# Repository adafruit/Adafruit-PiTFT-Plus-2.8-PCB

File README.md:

## Adafruit PiTFT 2.8 Plus PCB

&nbsp; 
<br/>
Click the image or links below to go to a specific product in the Adafruit shop.

PCB files for the Adafruit PiTFT Plus 2.8" Display. Format is EagleCAD schematic and board layout
* Resistive Screen https://www.adafruit.com/product/2298
* Capacitive Touch Screen https://www.adafruit.com/product/2423

### DESCRIPTION
Are these not the cutest little displays for the Raspberry Pi? They feature a 2.8" display with 320x240 16-bit color pixels and a  resistive touchscreen or capacitive touch overlay..

This updated design fits perfectly onto the Pi Zero, Pi 3, Pi 2 or Model A+, B+! (Any Pi with a 2x20 connector) Not for use with an old Pi 1 with 2x13 connector If you'd like to use a 2.8" display with the original Pi A or Pi B, check out the Model B version. This version also has all 40 pins GPIO pins brought out so you can connect a 40-pin GPIO cable underneath. Now that it's the same outline as a Pi 3/2/B+ it fits well on top of a Pi in our Raspberry Pi Enclosure base and can use our faceplate for a compact touchscreen Pi

The display and touchscreen uses the hardware I2C Pins (SDA & SCL), SPI pins (SCK, MOSI, MISO, CE0) as well as GPIO #25 and #24. All other GPIO are unused and you can still share the I2C pins with sensors, LED drivers, etc. Since we had a tiny bit of space, there's 4 slim tactile switches wired to four GPIOs, that you can use if you want to make a basic user interface. For example, you can use one as a power on/off button.

### License

Adafruit invests time and resources providing this open source design, please support Adafruit and open-source hardware by purchasing products from [Adafruit.com](https://www.adafruit.com)!

Creative Commons Attribution, Share-Alike license, check license.txt for more information All text above must be included in any redistribution - 
See license.txt for more information.

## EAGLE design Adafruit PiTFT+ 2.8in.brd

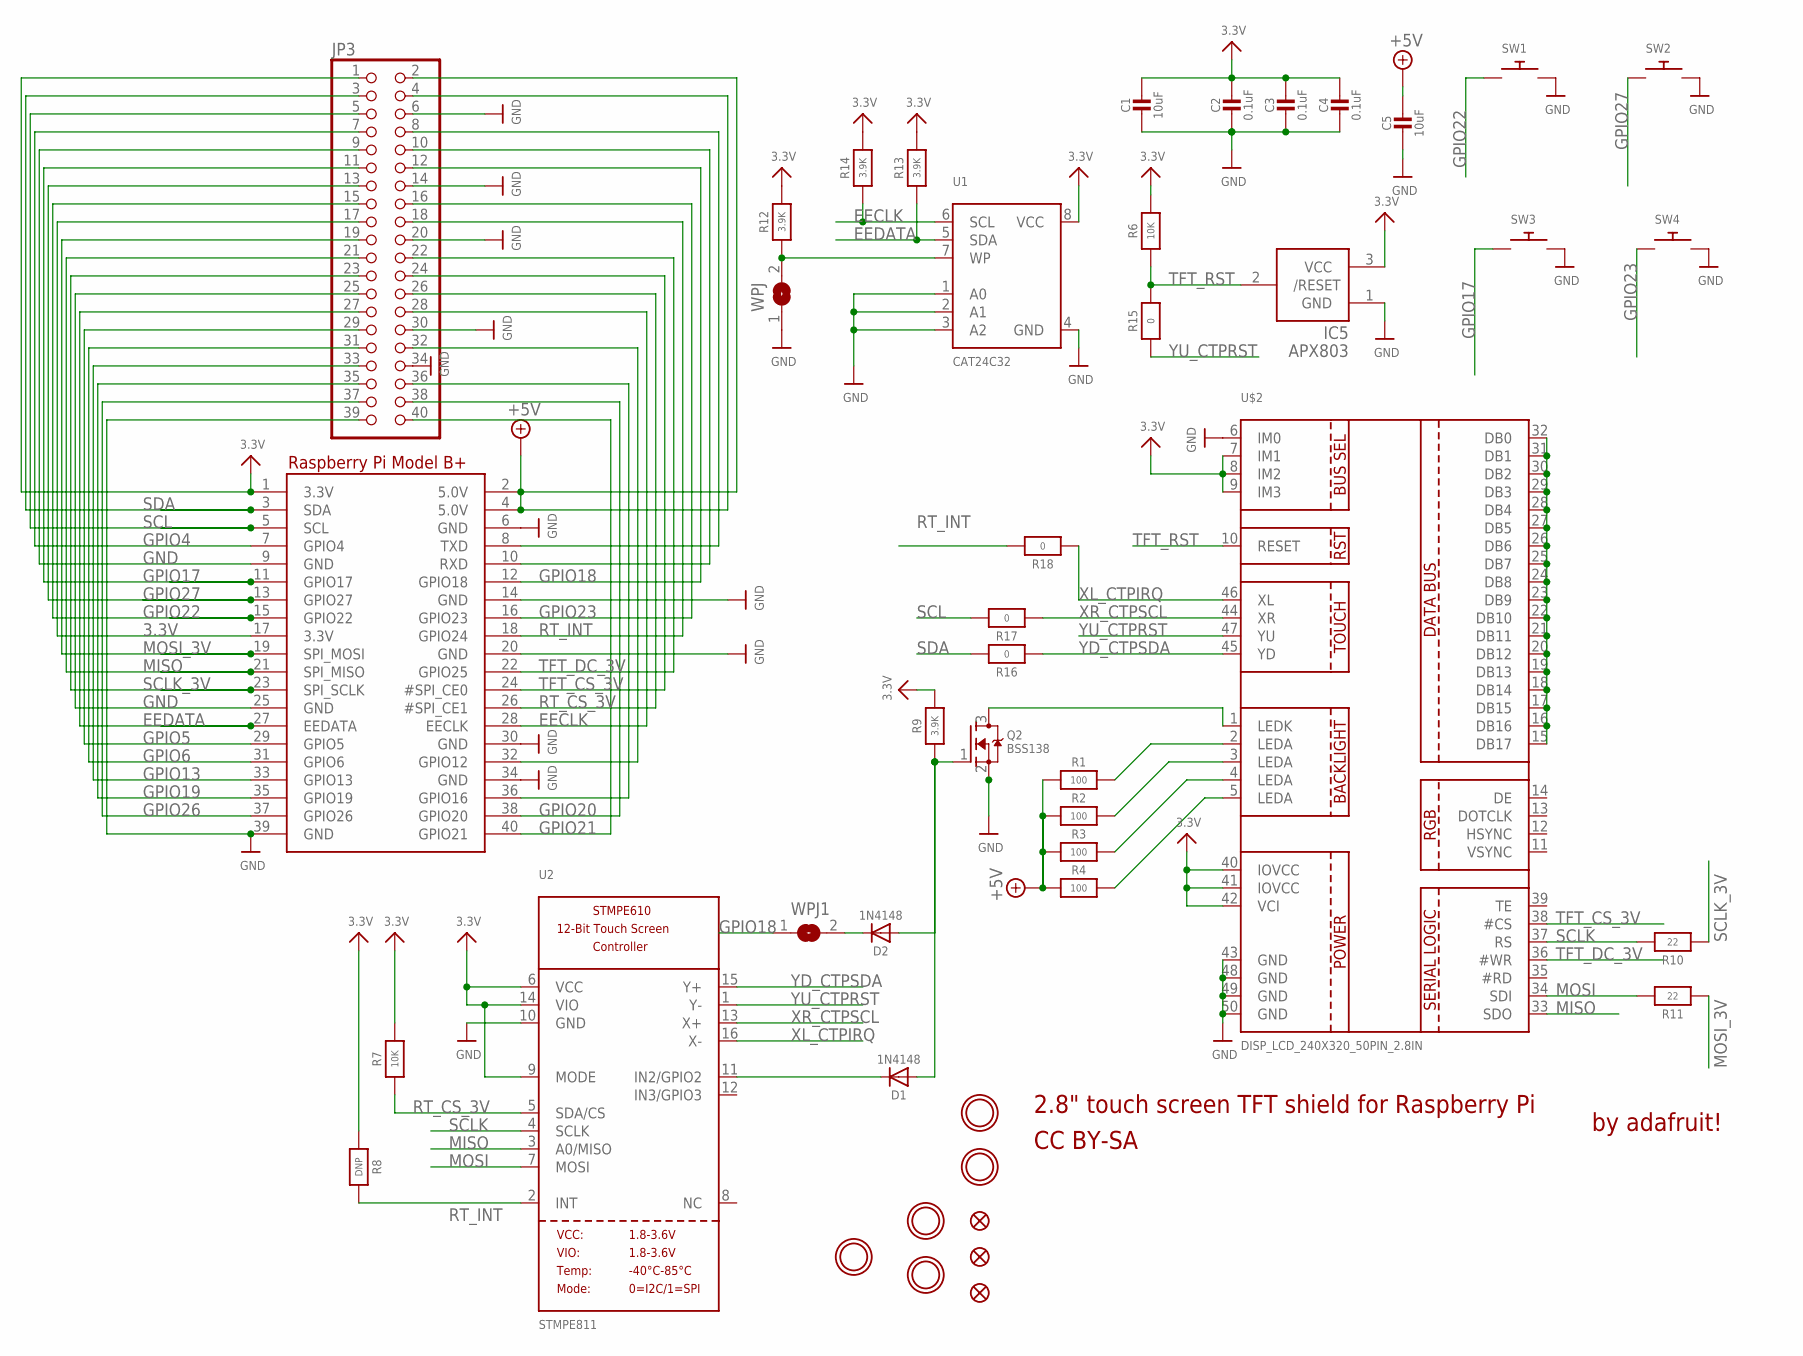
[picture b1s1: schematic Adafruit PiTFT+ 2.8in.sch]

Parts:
C1, C5: 10uF; 0805-NO
C2, C3, C4: 0.1uF; 0805-NO
D1, D2: 1N4148; SOD-323
IC5: APX803; SOT23
JP3: PINHD-2X20_SMT; 2X20_SMT_MALE
Q2: BSS138; SOT23-WIDE
R1, R2, R3, R4: 100; 0805-NO
R6, R7: 10K; 0805-NO
R8: DNP; 0805-NO
R9, R12, R13, R14: 3.9K; 0805-NO
R10, R11: 22; 0805-NO
R15, R16, R17, R18: 0; 0805-NO
RPI1: RASPBERRYPI_BPLUS_SHIELD_NODIM
SW1, SW2, SW3, SW4: SWITCH_PUSHBUTTONEVQ-PE; TACT_PANA-EVQ
U1: CAT24C32; SOIC8_150MIL
U2: STMPE811; QFN16_3MM
U$2: DISP_LCD_240X320_50PIN_2.8IN; TFT_2.83IN_240X320_50PIN
U$3, U$15, U$16, U$17, U$40: MOUNTINGHOLE3.0THIN; MOUNTINGHOLE_3.0_PLATEDTHIN
U$10, U$11, U$18: FIDUCIAL""; FIDUCIAL_1MM
WPJ, WPJ1: SOLDERJUMPERCLOSED; SOLDERJUMPER_CLOSEDWIRE

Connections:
3.3V: C1.1, C2.1, C3.1, C4.1, IC5.3 (VCC), JP3.1, JP3.17, R6.2, R7.2, R8.1, R9.2, R12.2, R13.2, R14.2, RPI1.1 (3.3V), RPI1.17 (3.3V), U1.8 (VCC), U2.6 (VCC), U2.9 (MODE), U2.14 (VIO), U$2.7 (IM1), U$2.8 (IM2), U$2.9 (IM3), U$2.40 (IOVCC), U$2.41 (IOVCC), U$2.42 (VCI)
+5V: C5.1, JP3.2, JP3.4, R1.1, R2.1, R3.1, R4.1, RPI1.2 (5.0V), RPI1.4 (5.0V)
EECLK: JP3.28, R14.1, RPI1.28 (EECLK), U1.6 (SCL)
EEDATA: JP3.27, R13.1, RPI1.27 (EEDATA), U1.5 (SDA)
GND: C1.2, C2.2, C3.2, C4.2, C5.2, IC5.1 (GND), JP3.6, JP3.9, JP3.14, JP3.20, JP3.25, JP3.30, JP3.34, JP3.39, Q2.2 (S), RPI1.6 (GND), RPI1.9 (GND), RPI1.14 (GND), RPI1.20 (GND), RPI1.25 (GND), RPI1.30 (GND), RPI1.34 (GND), RPI1.39 (GND), SW1.P$2, SW2.P$2, SW3.P$2, SW4.P$2, U1.1 (A0), U1.2 (A1), U1.3 (A2), U1.4 (GND), U2.10 (GND), U$2.6 (IM0), U$2.43 (GND), U$2.48 (GND), U$2.49 (GND), U$2.50 (GND), WPJ.1
GPIO4: JP3.7, RPI1.7 (GPIO4)
GPIO5: JP3.29, RPI1.29 (GPIO5)
GPIO6: JP3.31, RPI1.31 (GPIO6)
GPIO12: JP3.32, RPI1.32 (GPIO12)
GPIO13: JP3.33, RPI1.33 (GPIO13)
GPIO16: JP3.36, RPI1.36 (GPIO16)
GPIO17: JP3.11, RPI1.11 (GPIO17), SW3.P$1
GPIO18: JP3.12, RPI1.12 (GPIO18), WPJ1.1
GPIO19: JP3.35, RPI1.35 (GPIO19)
GPIO20: JP3.38, RPI1.38 (GPIO20)
GPIO21: JP3.40, RPI1.40 (GPIO21)
GPIO22: JP3.15, RPI1.15 (GPIO22), SW1.P$1
GPIO23: JP3.16, RPI1.16 (GPIO23), SW4.P$1
GPIO26: JP3.37, RPI1.37 (GPIO26)
GPIO27: JP3.13, RPI1.13 (GPIO27), SW2.P$1
MISO: JP3.21, RPI1.21 (SPI_MISO), U2.3 (A0/MISO), U$2.33 (SDO)
MOSI: R11.2, U2.7 (MOSI), U$2.34 (SDI)
MOSI_3V: JP3.19, R11.1, RPI1.19 (SPI_MOSI)
unnamed: Q2.3 (D), U$2.1 (LEDK)
unnamed: R1.2, U$2.2 (LEDA)
unnamed: R2.2, U$2.3 (LEDA)
unnamed: R3.2, U$2.4 (LEDA)
unnamed: D1.C, U2.11 (IN2/GPIO2)
unnamed: D2.C, WPJ1.2
unnamed: U$2.15 (DB17), U$2.16 (DB16), U$2.17 (DB15), U$2.18 (DB14), U$2.19 (DB13), U$2.20 (DB12), U$2.21 (DB11), U$2.22 (DB10), U$2.23 (DB9), U$2.24 (DB8), U$2.25 (DB7), U$2.26 (DB6), U$2.27 (DB5), U$2.28 (DB4), U$2.29 (DB3), U$2.30 (DB2), U$2.31 (DB1), U$2.32 (DB0)
unnamed: R4.2, U$2.5 (LEDA)
unnamed: R12.1, U1.7 (WP), WPJ.2
unnamed: D1.A, D2.A, Q2.1 (G), R9.1
RT_CS_3V: JP3.26, R7.1, RPI1.26 (#SPI_CE1), U2.5 (SDA/CS)
RT_INT: JP3.18, R8.2, R18.2, RPI1.18 (GPIO24), U2.2 (INT)
RXD: JP3.10, RPI1.10 (RXD)
SCL: JP3.5, R17.2, RPI1.5 (SCL)
SCLK: R10.2, U2.4 (SCLK), U$2.37 (RS)
SCLK_3V: JP3.23, R10.1, RPI1.23 (SPI_SCLK)
SDA: JP3.3, R16.2, RPI1.3 (SDA)
TFT_CS_3V: JP3.24, RPI1.24 (#SPI_CE0), U$2.38 (#CS)
TFT_DC_3V: JP3.22, RPI1.22 (GPIO25), U$2.36 (#WR)
TFT_RST: IC5.2 (/RESET), R6.1, R15.2, U$2.10 (RESET)
TXD: JP3.8, RPI1.8 (TXD)
XL_CTPIRQ: R18.1, U2.16 (X-), U$2.46 (XL)
XR_CTPSCL: R17.1, U2.13 (X+), U$2.44 (XR)
YD_CTPSDA: R16.1, U2.15 (Y+), U$2.45 (YD)
YU_CTPRST: R15.1, U2.1 (Y-), U$2.47 (YU)

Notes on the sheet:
2.8" touch screen TFT shield for Raspberry Pi
by adafruit!
CC BY-SA

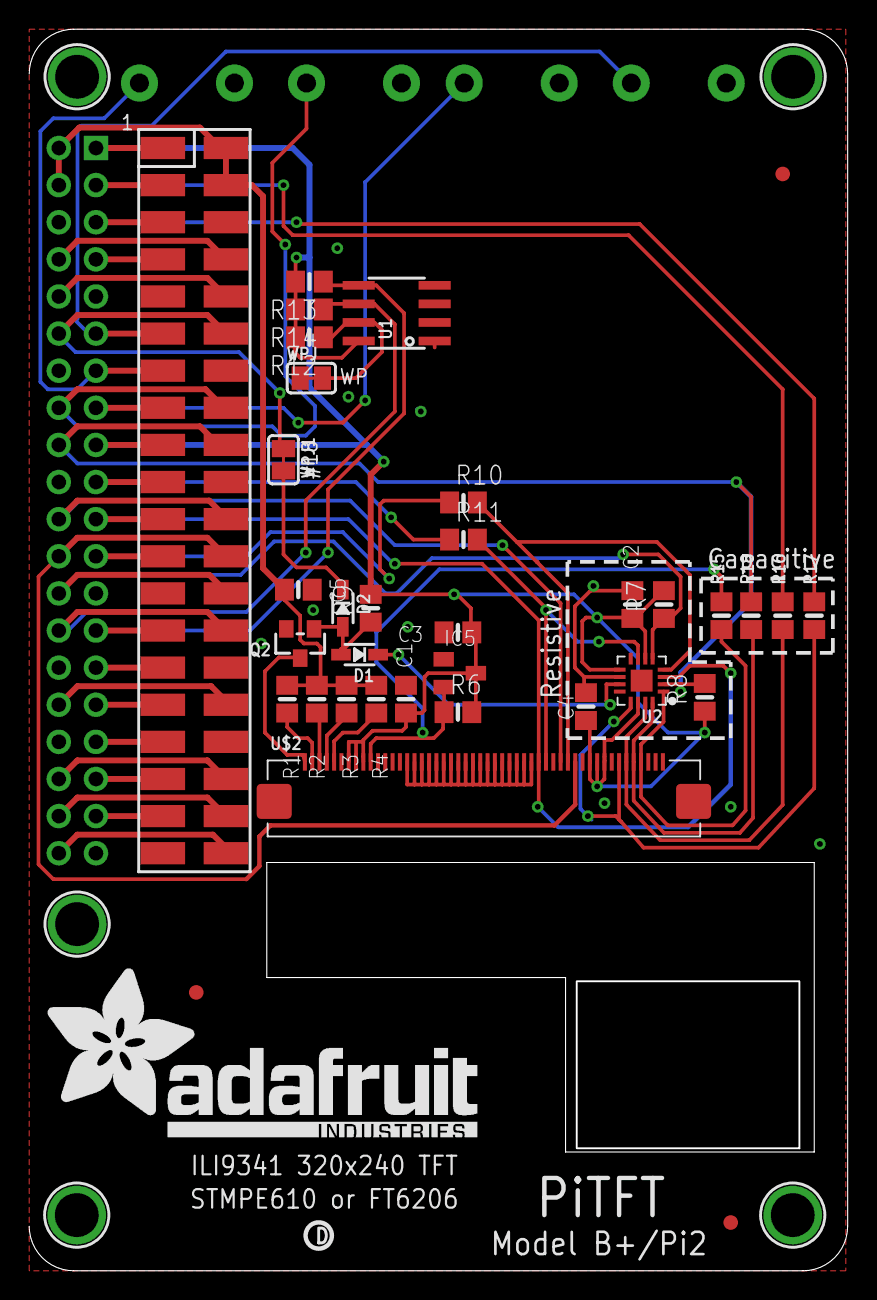
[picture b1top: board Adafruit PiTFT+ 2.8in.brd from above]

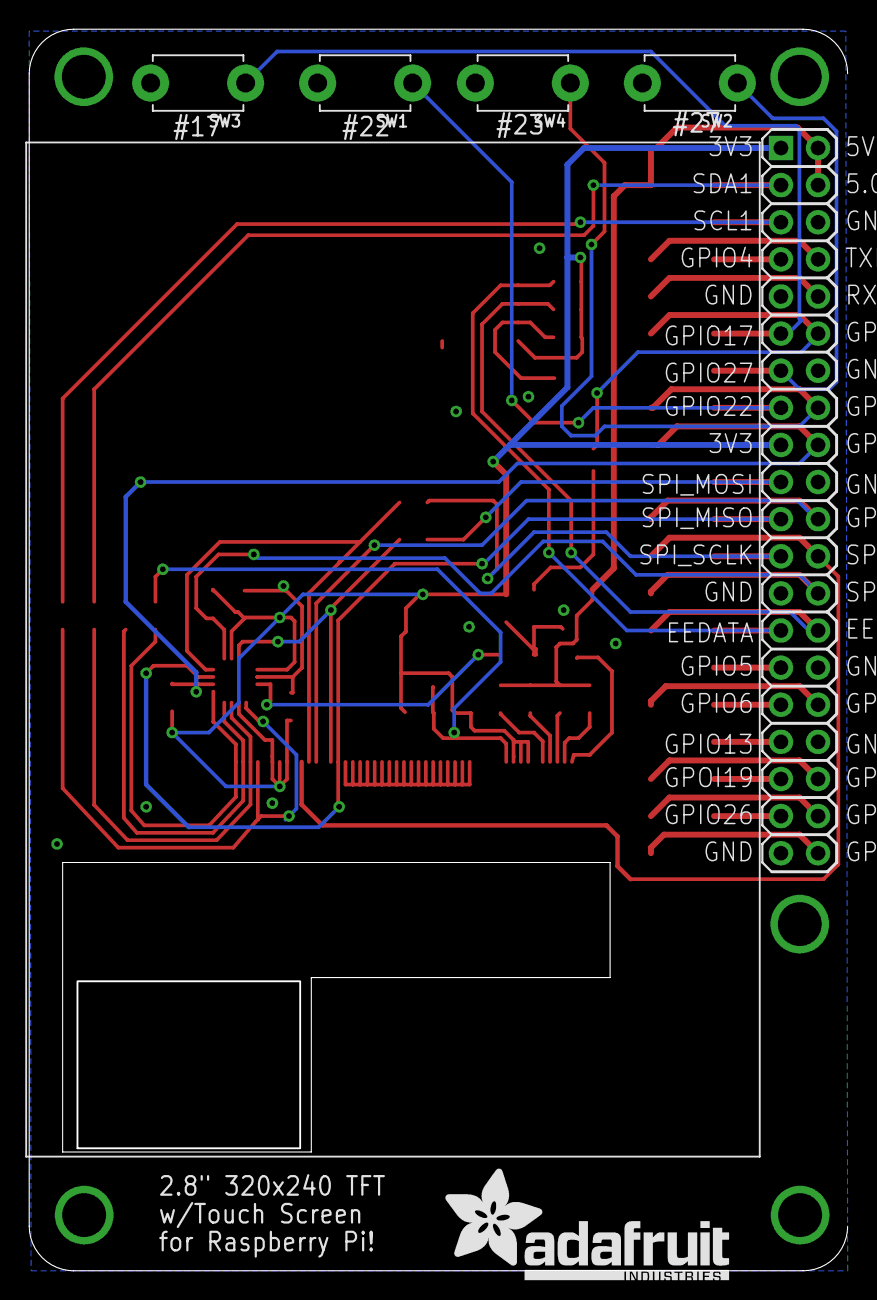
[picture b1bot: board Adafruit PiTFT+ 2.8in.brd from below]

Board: 2 copper layers, 55.9 x 84.8 mm, 48 parts (7 on the bottom side), 48 nets.

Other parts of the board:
U$12: PCBFEAT-REV-040
U$23: ADAFRUIT_TEXT_20MM
U$42: ADAFRUIT_TEXT_30MM

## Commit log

2016-07-15 plus!
2016-10-01 add captouch plus
